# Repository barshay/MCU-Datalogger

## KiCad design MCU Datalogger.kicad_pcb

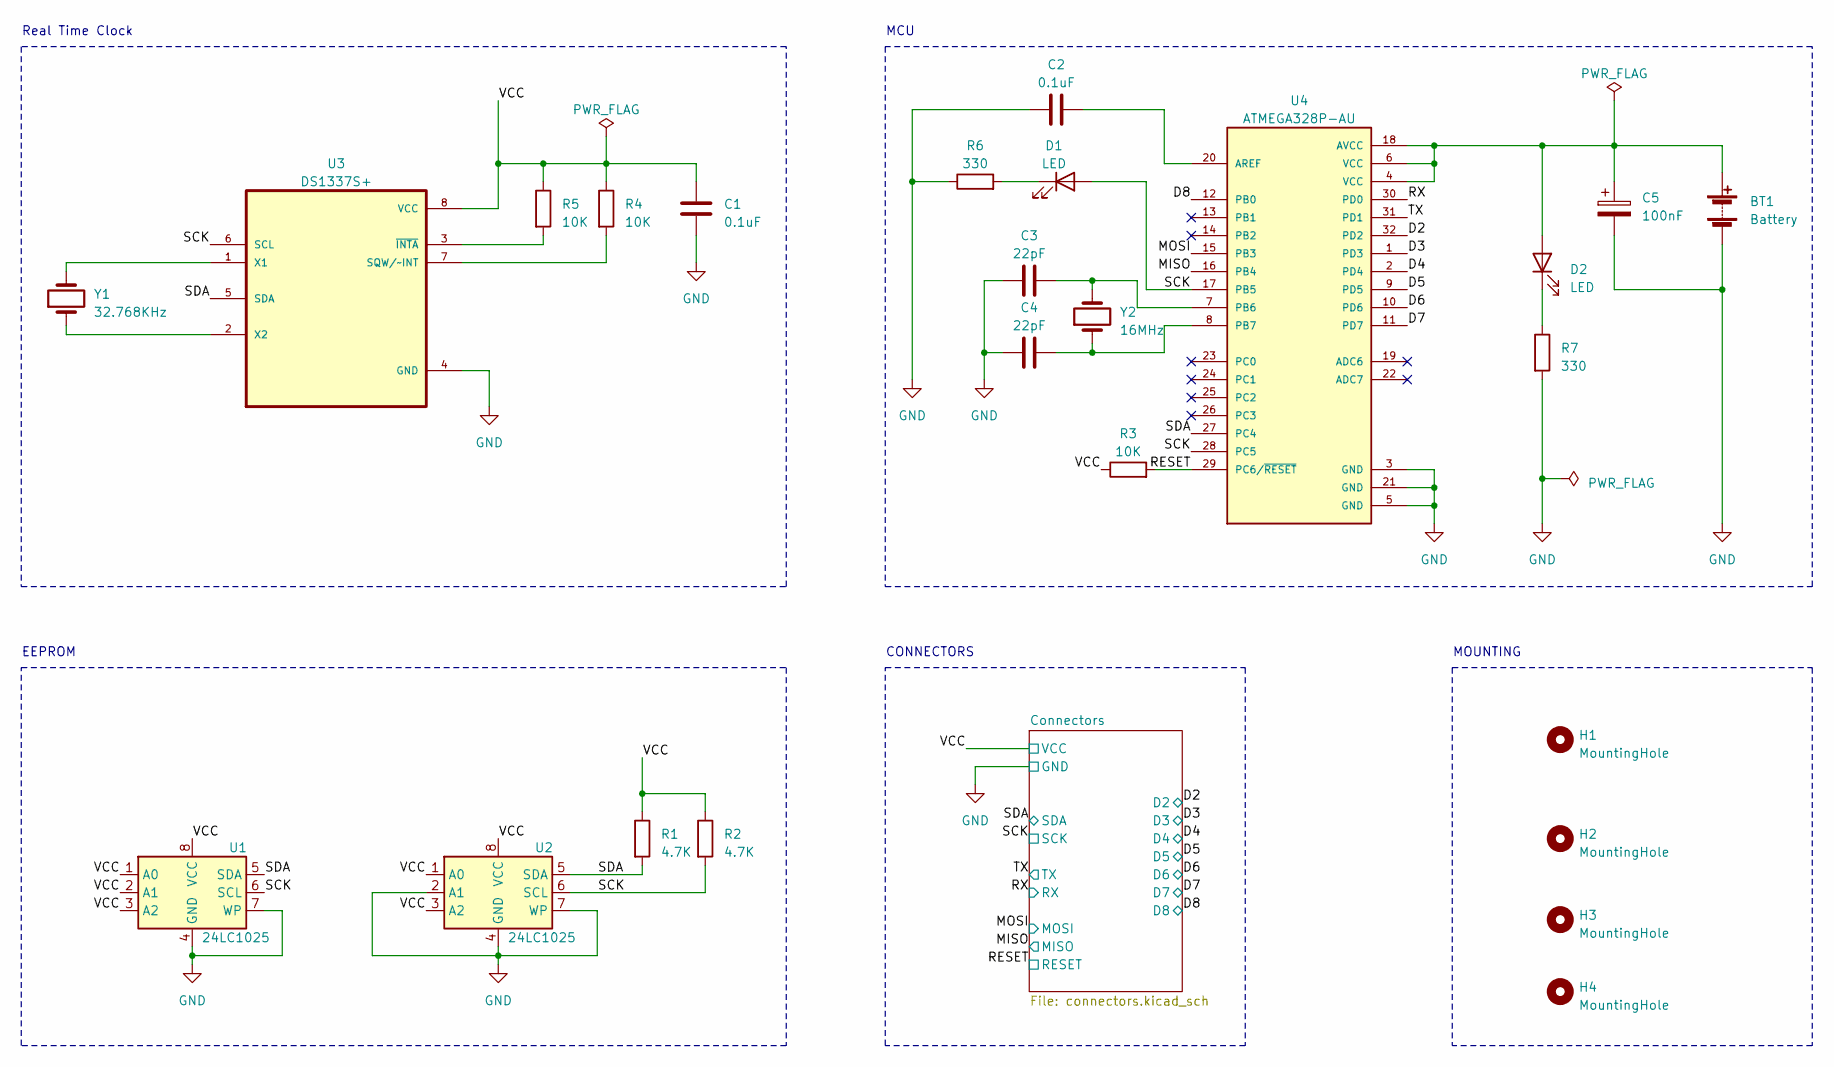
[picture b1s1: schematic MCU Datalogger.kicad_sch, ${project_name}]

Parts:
BT1: Battery; PinHeader_1x02_P2.54mm_Vertical
C1, C2: 0.1uF; C_0805_2012Metric
C3, C4: 22pF; C_0805_2012Metric
C5: 100nF; C_0805_2012Metric
D1, D2: LED; LED_0805_2012Metric
H1, H2, H3, H4: MountingHole; MountingHole_2.1mm
R1, R2: 4.7K; R_0805_2012Metric
R3, R4, R5: 10K; R_0805_2012Metric
R6, R7: 330; R_0805_2012Metric
U1, U2: 24LC1025; SOIC-8_5.23x5.23mm_P1.27mm
U3: DS1337S+; SOIC127P600X175-8N
U4: ATMEGA328P-AU; QFP80P900X900X120-32N
Y1: 32.768KHz; Crystal_SMD_5032-2Pin_5.0x3.2mm_HandSoldering
Y2: 16MHz; Crystal_SMD_5032-2Pin_5.0x3.2mm_HandSoldering

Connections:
/D2: U4.32 (PD2); also elsewhere on the board
/D3: U4.1 (PD3); also elsewhere on the board
/D4: U4.2 (PD4); also elsewhere on the board
/D5: U4.9 (PD5); also elsewhere on the board
/D6: U4.10 (PD6); also elsewhere on the board
/D7: U4.11 (PD7); also elsewhere on the board
/D8: U4.12 (PB0); also elsewhere on the board
/MISO: U4.16 (PB4); also elsewhere on the board
/MOSI: U4.15 (PB3); also elsewhere on the board
/RESET: R3.2, U4.29 (PC6/~RESET); also elsewhere on the board
/RX: U4.30 (PD0); also elsewhere on the board
/SCK: D1.2 (A), R2.2, U1.6 (SCL), U2.6 (SCL), U3.6 (SCL), U4.17 (PB5), U4.28 (PC5); also elsewhere on the board
/SDA: R1.2, U1.5 (SDA), U2.5 (SDA), U3.5 (SDA), U4.27 (PC4); also elsewhere on the board
/TX: U4.31 (PD1); also elsewhere on the board
/VCC: C1.1, R1.1, R2.1, R3.1, R4.1, R5.1, U1.1 (A0), U1.2 (A1), U1.3 (A2), U1.8 (VCC), U2.1 (A0), U2.3 (A2), U2.8 (VCC), U3.8 (VCC); also elsewhere on the board
GND: BT1.2 (-), C1.2, C2.1, C3.1, C4.1, C5.2, R6.1, R7.2, U1.4 (GND), U1.7 (WP), U2.2 (A1), U2.4 (GND), U2.7 (WP), U3.4 (GND), U4.3 (GND), U4.5 (GND), U4.21 (GND); also elsewhere on the board
unnamed: BT1.1 (+), C5.1, D2.2 (A), U4.4 (VCC), U4.6 (VCC), U4.18 (AVCC)
unnamed: D1.1 (K), R6.2
unnamed: D2.1 (K), R7.1
unnamed: R4.2, U3.7 (SQW/~INT)
unnamed: U3.1 (X1), Y1.2
unnamed: U3.2 (X2), Y1.1
unnamed: R5.2, U3.3 (~INTA)
unnamed: C2.2, U4.20 (AREF)
unnamed: C3.2, U4.7 (PB6), Y2.2
unnamed: C4.2, U4.8 (PB7), Y2.1

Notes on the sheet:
EEPROM
MCU
MOUNTING
CONNECTORS
Real Time Clock

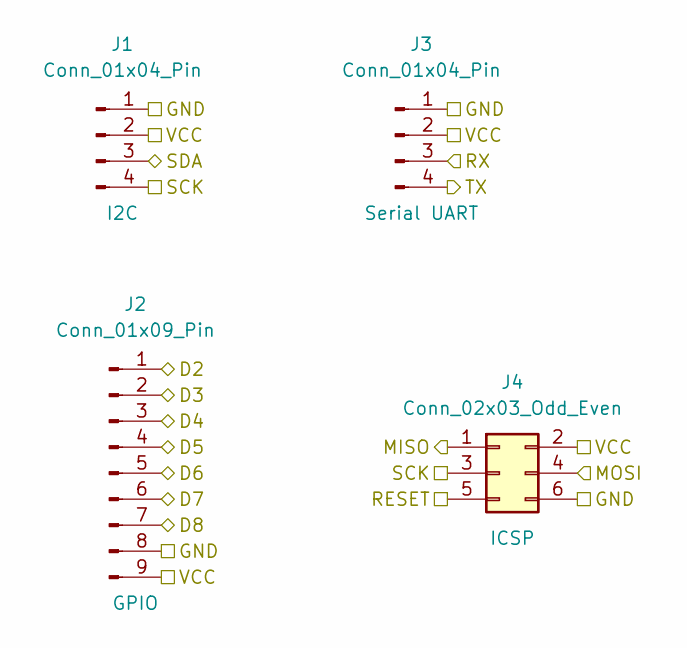
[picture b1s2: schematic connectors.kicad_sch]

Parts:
J1, J3: Conn_01x04_Pin; PinHeader_1x04_P2.54mm_Vertical
J2: Conn_01x09_Pin; PinHeader_1x09_P2.54mm_Vertical
J4: Conn_02x03_Odd_Even; PinHeader_2x03_P2.54mm_Vertical

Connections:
/D2: J2.1; also elsewhere on the board
/D3: J2.2; also elsewhere on the board
/D4: J2.3; also elsewhere on the board
/D5: J2.4; also elsewhere on the board
/D6: J2.5; also elsewhere on the board
/D7: J2.6; also elsewhere on the board
/D8: J2.7; also elsewhere on the board
/MISO: J4.1; also elsewhere on the board
/MOSI: J4.4; also elsewhere on the board
/RESET: J4.5; also elsewhere on the board
/RX: J3.3; also elsewhere on the board
/SCK: J1.4, J4.3; also elsewhere on the board
/SDA: J1.3; also elsewhere on the board
/TX: J3.4; also elsewhere on the board
/VCC: J1.2, J2.9, J3.2, J4.2; also elsewhere on the board
GND: J1.1, J2.8, J3.1, J4.6; also elsewhere on the board

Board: 2 copper layers, 29 parts (0 on the bottom side), 26 nets, no tracks yet.

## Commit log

2023-06-18 First commit of new project
2023-06-18 Have added required symbols to the schematic sheets
2023-06-19 Changed locations of symbols (arrange)
2023-06-19 Added component values
2023-06-19 Completed symbol-footprint associations
2023-06-20 Completed wiring of main sheet
2023-06-25 Completed wiring in the second sheet.
2023-07-02 Allocated GND and VCC nets to the Power net class
2023-07-02 Completed comments
2023-07-03 Setup Pcbnew
